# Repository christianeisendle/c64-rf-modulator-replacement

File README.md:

# C64 RF Modulator Replacement
## Introduction
This is yet another C64 RF Modulator replacement. Strictly seen, it doesn't fully replace the RF modulation (used to connect to the antenna input of old CRT TV sets) but addresses some well known
issues of the existing RF modulator with respect to generation of the Luma and Chroma signals for S-Video related to signal quality and levels.

## Features
- S-Video Mini-DIN connector at physical location of the legcy RF Cinch connector
- Separate processing of S-Video (Luma/Chroma) for S-Video connector and C64 on-board DIN video connector
- Composite Video signal generation for C64 video connector
- 4 layer PCB design to ensure high signal integrity

## Design
The [schematic](schematic.pdf) shows the 4 different blocks used in the design:
- **Power section:**
Generates a clean 3.3V supply using an LDO out of the 5V system supply
- **C64 Interface & Input Divider stage:**
Incoming Luma and Chroma signals are open drain and open source signals, respectively. The input stage adds needed pull-up/down resistor network along with some
triming resistors to configure the proper input levels
- **Video Amplifier S-Video:**
The input signals are amplified/buffers by a THS-7314 video amplifier with a gain of 6dB. This 6dB compensates for the 6dB drop at the receiving device due to the 75 Ohms serial and end termination which means, the input signal at THS-7314 has the same level as the input signal of the receiving device. Note that THS-7314 has an internal bias circuitry which allows AC coupling of the input signal using 100nF capcitors C7 and C8. The output is DC coupled as the design intentionally avoids AC coupling capacitors which would be quite large for a 75 Ohms line. It is
known practice that AC coupling typically happens at the input stage of the receiving device.
- **Video Amplifier C64 Interface:**
This stage is similar to the S-Video stage but in addition it generates the Composite Video for the C64 Video connector. In case this is not needed, R3, R4, R7 and C6 can be left out.

## Triming Procedure
Two testpoints are available at the input of video amplifier U3: 

The testpoint labeled C exposes the Chroma signal and L the Luma signal. Next two these two testpoints there are vias (blue circled) with removed solder mask which can be used for low-inductive probing. Power up the C64 without a screen connected. Connect a scope to the testpoints and use the corresponding Luma and Chroma trimmer (right in the picture) to adjust the required signal levels:
- **Chroma:** 0.3Vpp
- **Luma:** 1Vpp

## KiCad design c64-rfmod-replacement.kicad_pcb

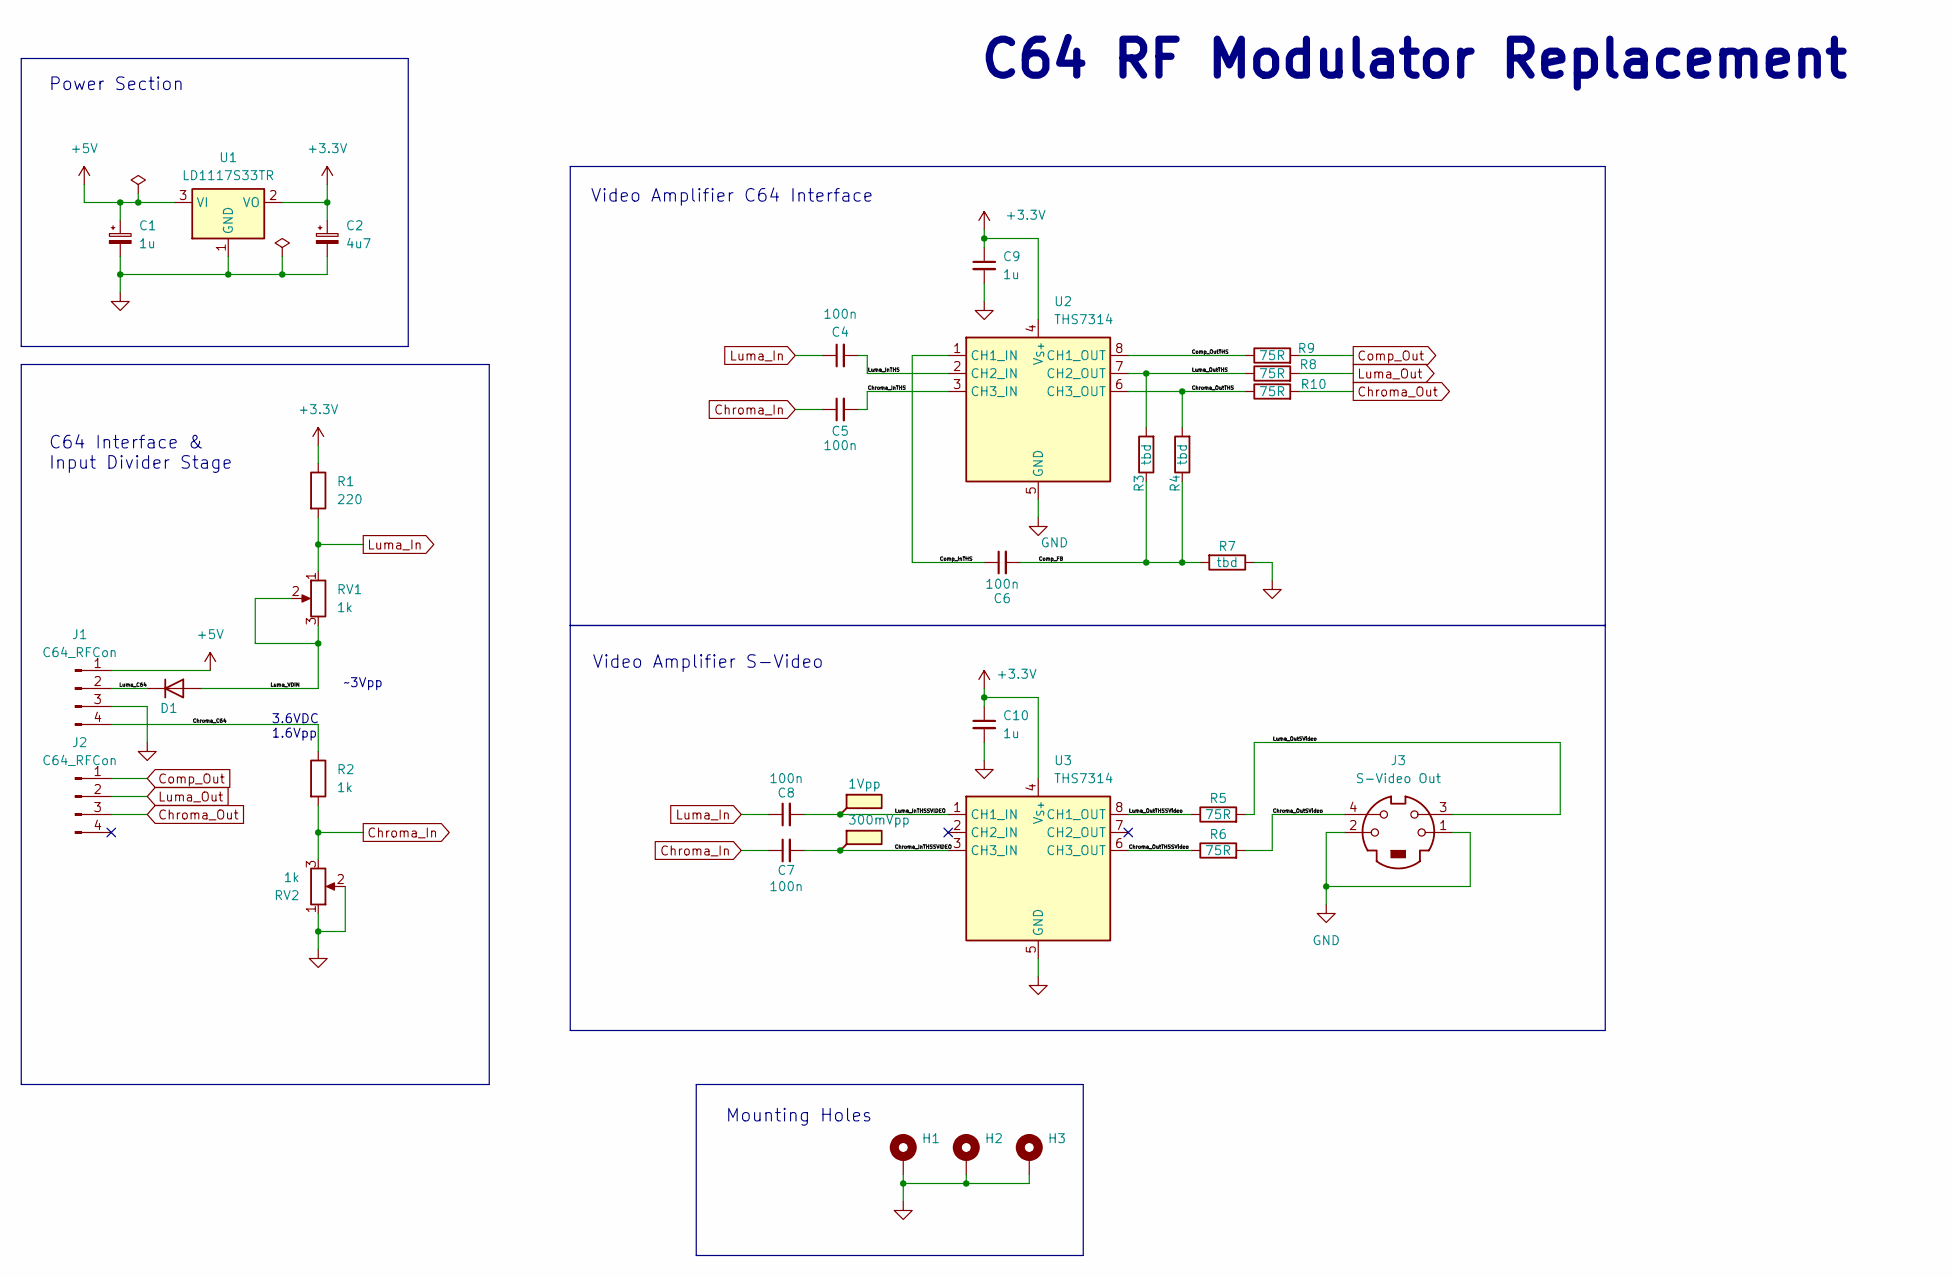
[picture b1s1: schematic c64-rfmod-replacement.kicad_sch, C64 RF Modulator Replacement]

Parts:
C1, C9, C10: 1u; C_0603_1608Metric
C2: 4u7; C_1206_3216Metric
C4, C5, C6, C7, C8: 100n; C_0603_1608Metric
D1: 1N4148WT; D_MiniMELF
H1, H2, H3: MountingHole_Pad; MountingHoleLong
J1, J2: C64_RFCon; PinHeader_1x04_P2.54mm_Vertical
J3: S-Video Out; MD2-40ST-SMT
R1: 220; R_0603_1608Metric
R2: 1k; R_0603_1608Metric
R3, R4, R7: tbd; R_0603_1608Metric
R5, R6, R8, R9, R10: 75R; R_0603_1608Metric
RV1, RV2: 1k; Potentiometer_Vishay_TS53YL_Vertical
TP1: 1Vpp
TP2: 300mVpp
U1: LD1117S33TR; SOT-223-3_TabPin2
U2, U3: THS7314; SOIC-8_3.9x4.9mm_P1.27mm

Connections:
+3.3V: C2.1, C9.1, C10.1, R1.1, U1.2 (VO), U2.4 (V_{S+}), U3.4 (V_{S+})
+5V: C1.1, J1.1, U1.3 (VI)
/Chroma_C64: J1.4, R2.1
/Chroma_InTHS: C5.2, U2.3 (CH3_IN)
/Chroma_InTHSSVIDEO: C7.2, TP2.1, U3.3 (CH3_IN)
/Chroma_OutSVideo: J3.4, R6.2
/Chroma_OutTHS: R4.2, R10.1, U2.6 (CH3_OUT)
/Chroma_OutTHSSVideo: R6.1, U3.6 (CH3_OUT)
/Comp_FB: C6.2, R3.1, R4.1, R7.2
/Comp_InTHS: C6.1, U2.1 (CH1_IN)
/Comp_OutTHS: R9.1, U2.8 (CH1_OUT)
/Luma_C64: D1.1 (K), J1.2
/Luma_InTHS: C4.2, U2.2 (CH2_IN)
/Luma_InTHSSVIDEO: C8.2, TP1.1, U3.1 (CH1_IN)
/Luma_OutSVideo: J3.3, R5.2
/Luma_OutTHS: R3.2, R8.1, U2.7 (CH2_OUT)
/Luma_OutTHSSVideo: R5.1, U3.8 (CH1_OUT)
/Luma_VDIN: D1.2 (A), RV1.2, RV1.3
Chroma_In: C5.1, C7.1, R2.2, RV2.3
Chroma_Out: J2.3, R10.2
Comp_Out: J2.1, R9.2
GND: C1.2, C2.2, C9.2, C10.2, H1.1 (1_1), H2.1 (1_1), H3.1 (1_1), J1.3, J3.1, J3.2, J3.SH, R7.1, RV2.1, RV2.2, U1.1 (GND), U2.5 (GND), U3.5 (GND)
Luma_In: C4.1, C8.1, R1.2, RV1.1
Luma_Out: J2.2, R8.2

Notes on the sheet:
C64 RF Modulator Replacement
Video Amplifier S-Video
Video Amplifier C64 Interface
C64 Interface & Input Divider Stage
Mounting Holes
Power Section
3.6VDC 1.6Vpp
~3Vpp

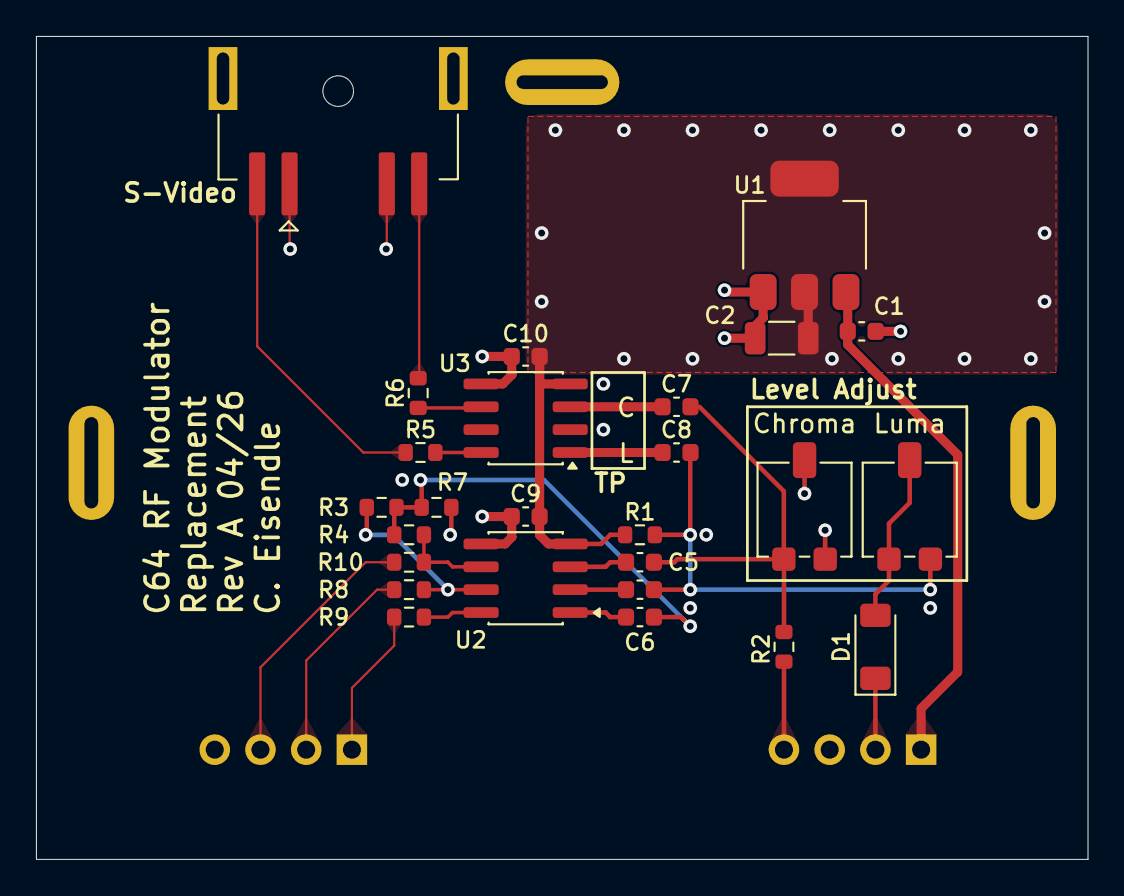
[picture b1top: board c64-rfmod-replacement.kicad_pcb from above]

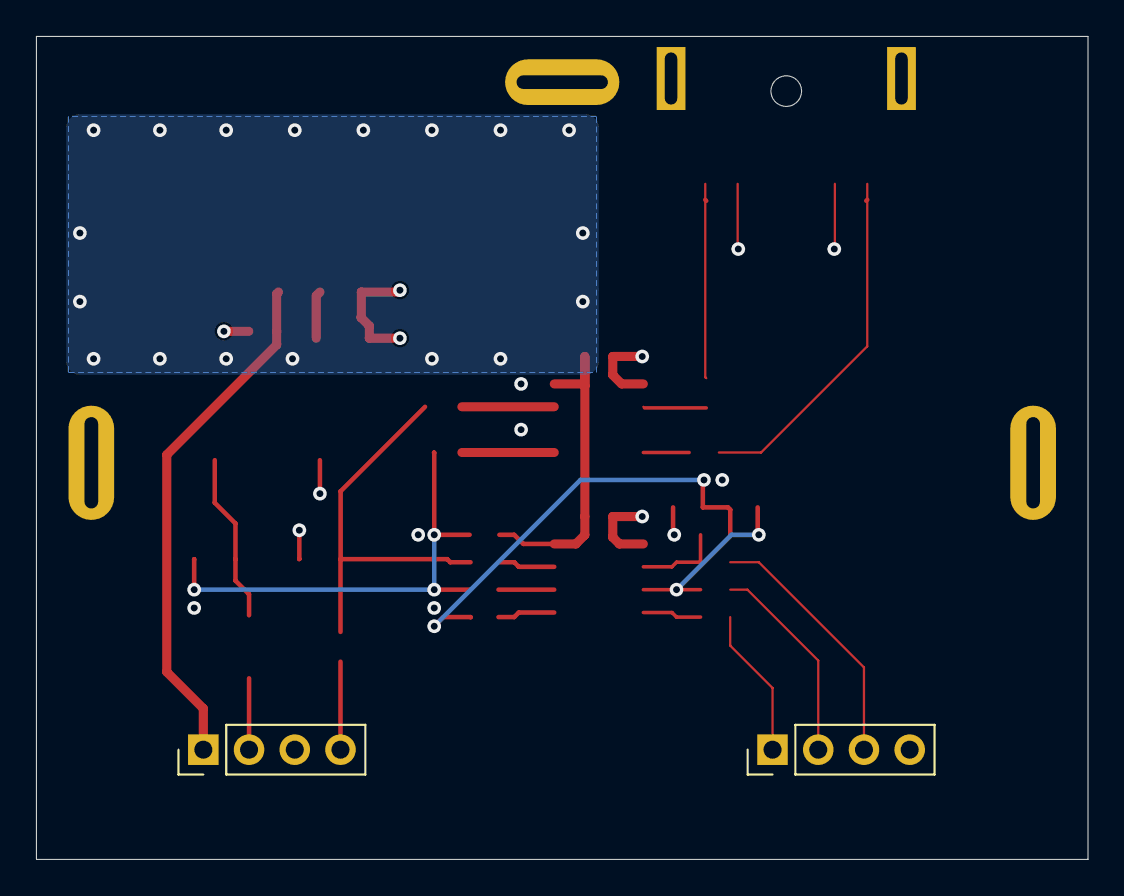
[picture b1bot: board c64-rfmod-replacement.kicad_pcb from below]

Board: 4 copper layers, 58.4 x 45.7 mm, 31 parts (2 on the bottom side), 24 nets.

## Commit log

2026-04-26 Initial commit (=Rev A)
2026-04-26 Add readme
2026-04-26 Add 3D model for trimmers
